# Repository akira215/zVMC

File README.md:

# zVMC
Driving ALDES controlled mechanical ventilation using Modbus, embedded sofware on dedicated PCB using ESP32C6 µC

# Description

This repository contain all the development for an electronic device that will monitor ALDES VMC Inspirair using zigbee to transmit data to a coordinator. It contains: 
 * A PCB design [PCB design](PCB/README.md)
 * An enclosure design to be printed in 3D [Enclosure design](3Dprint/README.md)
 * Source code of the embedded software on the board (in an ESP32C6 µC)
 * An External converter for Zigbee2MQTT service [external converter](external_converters)

# Principle

The board will collect data from various sensors surch as:
 * Upstream static pressure (pump side)
 * Downstream static pressure (home side) - difference between upstream and downstream static pressure is used to estimate filters clogging
 * Water level sensor, to estimate the available water volume in the tank
 * water pulse meter to count the consumption in the home
 * Additionally on board temperature sensor could be monitor

 The 3 first sensors shall be 4-20mA sensor directly connected to the board. The water counter shall be a dry contact meter, connected to the board

 All these sensors have a calibration factor that can be updated directly form Zigbee2MQTT GUI. To avoid losing calibration, the device itself will keep updated theses factor in its Non Volatile Storage.

A 4-20mA input is available for any other futher sensor requirement. Adding a sensor will require to :
 * Update the embedded software
 * Update the external converter on Zigbee2MQTT side

## Usage

  * Short press button to join the zigbee network (coordinator shall grant pairing) -> LED shall flash, until network is joined, it then shutoff
  * Long press button to leave network. When the LED is fixed on, the device is not connected to the network neither is trying to join

## Sensor selection

### Upstream and downstream static pressure

  Regular pressure transmitter are not so expensive and efficient for that purpose. These 2 sensors shall have a measured range according to installation pressure. In regular network, pressure is limited to 3 bars, so selecting a sensor 0-5 bars seems a good choice. If the upper value is higher, the resolution of the measurement will be less as the ADC converter resolution is fixed.

  The shunt to convert current to tension for the ADC converter is 133R, and Imax for the sensor @max range will be 20mA so Umax for ADS1115 will be 2.66V (U=R*I). 5 bars = 500 kPa, so the calibration factor shall be 500 kPa / 2.66V = 187.97 kPa/V. Of course this factor shall be adjusted by measuring at the same location of one sensor the pressure, and correcting the reading of the sensor, but this short computation can help to start setting up calibration factor

### Water level

  Whatever technology of sensor could be used as soon as its output is 4-20mA current. Tests have been done using submerged differential pressure sensor, with the balance pipe to get the atmospheric pressure that run with the electrical cable, they worked properly. The range of this sensor shall be in accordance with the depth of the tank. The output value of Zigbee2MQTT will be a % of depth (meaning 100% when tank is full). Depending on the shape and cross section of the tank, this could be converted to a volume directly in the Z2M external converter, or outside Z2M in another software.

  The shunt to convert current to tension for the ADC converter is 133R, and Imax for the sensor @max range will be 20mA so Umax for ADS1115 will be 2.66V (U=R*I). fFr 100% the calibration factor shall be 100% / 2.66V = 37.594 %/V. Of course this factor shall be adjusted when tank is full to read 100% in the Zigbee2MQTT output.

### Water pulse counter

  The water meter shall send a pulse each XX L, whatever XX is. It is expected to have a dry contact that switch on and off each pulse. Hardware debouncer has been implemented for a particular counter, measuring bouncing using an oscilloscope. Computation of this RC filter has been provided here:
  [Spreadsheet](<PCB/2024-06-29 Comput.ods>)
    
  The kFactor to be set up in Zigbee2MQTT is only the L per pulse of the counter.

## Zigbee2MQTT integration

### External converter

External converter shall be loaded according to Zigbee2MQTT instructions:

[Zigbee2MQTT external converters](https://www.zigbee2mqtt.io/advanced/more/external_converters.html)

Restart Zigbee2MQTT `Webpage > Settings > Tools > Restart Zigbee2MQTT`

### Pairing zTank device

If the LED is fixed on, short press one time on the button, this will put the device in pairing mode.
Device is in Pairing Mode when the LED flahes quickly. 

Put Coordinator (or other device) in pairing mode using Zigbee2MQTT GUI (antenna symbol on the upper right of the screen with mention `All`)

After a short time, LED shall stop flashing. When LED is off, device is paired. You can check on Zigbee2MQTT device list

### Device icon

To add an icon in Zigbee2MQTT GUI, create a folder named `device_icon` in the root of Zigbee2MQTT docker installation (folder containing `configuration.yml`). In that foler, put the `zTank_icon.png` file contained in the `img` directory of this repository.

On Zigbee2MQTT GUI, go to `Devices` list and click on the device. Go to `Settings` tab and scroll down to the `icon` box.
Put `device_icons/zTank_icon.png` in that box. Icon shall be visible on Zigbee2MQTT GUI.

### Reporting

To develop*******************************************************************

## Build Instructions

The embedded software required `esp-ash-components`:

```
git submodule add https://github.com/akira215/esp-ash-components.git components
```

Create a partition.csv for zigbee and configure menuconfig with custom partition table (shall be done by default)

## Remote USB over IP to debug

### Server side using raspberry Pi

Install package:

```
sudo apt install usbip
```

Install drivers and let them run at start:

```
sudo -i
modprobe usbip_host
echo 'usbip_host' >> /etc/modules
```

List usb devices:

```
usbip list -l
```

Create start and stop scripts:

```
nano /usr/sbin/usbip_start.sh
```

```
#! /bin/bash

usb1='303a:1001'
# usb2='xxx'

/usr/sbin/usbip bind --$(/usr/sbin/usbip list -p -l | grep '#usbid='$usb1'#' | cut '-d#' -f1)
#/usr/sbin/usbip bind --$(/usr/sbin/usbip list -p -l | grep '#usbid='$usb2'#' | cut '-d#' -f1)

```

```
nano /usr/sbin/usbip_stop.sh
```

```
#! /bin/bash

usb1='303a:1001'
# usb2='xxx'

/usr/sbin/usbip unbind --$(/usr/sbin/usbip list -p -l | grep '#usbid='$usb1'#' | cut '-d#' -f1)
#/usr/sbin/usbip unbind --$(/usr/sbin/usbip list -p -l | grep '#usbid='$usb2'#' | cut '-d#' -f1)
killall usbipd
```

Turn them executables:

```
chmod +x /usr/sbin/usbip_start.sh
chmod +x /usr/sbin/usbip_stop.sh
```

Test the scripts:

```
. /usr/sbin/usbip_start.sh
. /usr/sbin/usbip_stop.sh
```

Create a service:

```
nano /lib/systemd/system/usbipd.service
```

```
[Unit]
Description=usbip host daemon
After=network.target

[Service]
Type=forking
ExecStart=/usr/sbin/usbipd -D
ExecStartPost=/bin/sh -c '/usr/sbin/usbip_start.sh'
ExecStop=/bin/sh -c '/usr/sbin/usbip_stop.sh'

[Install]
WantedBy=multi-user.target
```

Start the service at boot:
let system know about that service

```
systemctl --system daemon-reload
```

to start service at boot

```
systemctl enable usbipd.service
```

and start service, check status:

```
systemctl start usbipd.service
systemctl status usbipd.service
```

### Client side Windows 11

Create a restore point on the system

Install OSSign release of https://github.com/vadimgrn/usbip-win2 :

https://github.com/OSSign/vadimgrn--usbip-win2/releases

run the GUI to find the device !

## Configuration

Configuration is available in `menuconfig` in the `Project setting` section:

### Pin Layout

  This section refer to hardware connection of LED button and volume meter. <span style="color:red">**These settings shall not be changed unless new hardware is developped.**</span>

### Zigbee endpoints

  This section refer to the endpoint for each sensor of the device. Any change in this number require to update the external converter accordingly

  And in Zigbee2MQTT external converter:

### Zigbee device

  Zigbee stack has been sized doing extensive tests. <span style="color:red">**This setting shall not be changed.**</span>

### ADS Pin Layout

  This section refer to hardware connection of ADS1115 converter to µC pin. <span style="color:red">**These settings shall not be changed unless new hardware is developped.**</span>

### ADS Converter config

  The first 3 inputs refer to the channel in which each sensor is connected. Take care that channel are not implemented on the connector in a logical order, so please refer to pictures that describe which pins of the connector is connected to which ADC channel (and polarity for sensors)

  The delay between 2 queries of ADS is the update rate of the measurement. Between 2 measurement, ADS is put in sleep to optimize consumption. Take care that driver will trigger one conversion for each channel, so there is a minimal time between 2 queries, depending on the resolution set for the ADS.

  The delay between 2 queries of temperature is the update rate of the measurement of the internal µC temperature sensor.

## Current Status

Still work in progress, but is completely running. All bugs 
could be reported to try to improve it.

## PCB design

[PCB design](PCB/README.md)

## Enclosure design design

[Enclosure design](3Dprint/README.md)

## Caveats

### To be developped

OTA update

## Usage and Examples

## Changes

### New in version 0.0.0

## Credits

 * [Zigbee2MQTT](https://github.com/Koenkk/zigbee2mqtt)

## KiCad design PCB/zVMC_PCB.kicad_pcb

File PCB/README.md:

# zTank PCB
A dedicated PCB using ESP32C6 µC as been designed to optimize reliability and costs.

## Tools

 The design of the PCB has been done with KiCad 9.0. Particular footprint and 3D STEP file are included in the `/footprints` folder for sake of maintenance

## Design

 The design is based on ESP32C6 WROOM with the following peripherials:
 * USB for power, flash device and output serial debug / info.
 * Powering circuit is done using MCP1826S 
 * A 4-20mA loop is built based on a LM2735X (1.6MHz) to raise voltage to about 20V
 * 4 channels 4-20mA sensors is provided and converted using ADS1115IDGS. It communicate with µC with i2c port
 * a debounced contact is provided for pulse counter
 * A push button is also provided for very simple HMI
 * PCB is also equipped by a LED for simpl HMI
 * Finally PCB is equipped with header that can be used for a touchscreen device in case of future needs (software lib already written and tested)

 Component size has been selected to 0805, except ESD protective diodes that are smaller.

### USB

  USB socket is grounded to the main ground planes (2 sides).
  USB Lines `USB-` and `USB+` are directly connected to ESP32C6 to flash and monitor µC.
  `VBUS` is used to provide `+5V` (which is in fact lower than +5V) via a protective diode `D3`.

  All this 3 lines are protected by ESD protective diode.

### Voltage regulator

  All the board is powered using `+3.3V`. This voltage is provided by a fixed low-voltage regulator MCP1826S-3302E that can provide up to 1000mA.
  Fixed voltage regulator requires only few external component, in this case only capacitors are installed as per datasheet.

### 4-20mA Voltage circuit

  To avoid noise on lines and due to voltage drop at each stage, 4-20mA loop voltage shall be at around 20V. Care shall be taken when changing this voltage as it may require adjustment (in the shunt values for instance) to avoid damaging other components.

  This voltage is produced from `+5V` using a boost type regulator LM2735X (@1.6MHz). Computation of the external components are provided in the LibreOffice Spreadsheet [PCB comput spreadsheet](<2024-06-29 Comput.ods>). A 33µH inductance has been selected to get a clean output voltage to avoid noise on sensors line.

### 4-20mA conversion

  4 channels are available via Phoenix contact 8 poles connector. Each channel input current is injected in a 133R shunt (low tolerance resistor) to output a voltage below 3.3V. A 100nF capacitor is provided to reduce noise.

  Each channel voltage is then converted in a digital signal using an ADS1115IDGS, that communicate with µC using i2c protocol. A ready pin is used to trigger an interrupt to the µC when data are available.
  External components are:
   * 10k resistor connected to the ground for the address of the device (only one on board so gnd is the common one)
   * 10k pull-up resistor on each signal (`SCL`, `SDA`, `RDY`) connected to µC
   * Decoupling capacitor for power lines and rearmable fuse to protect circuit

### Debounced contact

An harware RC filter has been set up on this input to avoid false triggering. The computation of this filter is detailed in the spreadsheet file [PCB comput spreadsheet](<2024-06-29 Comput.ods>), bouncing duration has been measured using an oscilloscope in a unique water meter equiped with dry contact pulse output. It may be required to adjust this filter if the water meter seems to input false pulse to the µC. 

The only other component is a pull-up resistor to not let a float input.

### µC ESP32C6 WROOM

ESP32C6 power up is done using decoupling capacitor (10µF // 100nF).

The `EN` pin is driven to the `+3.3V` to enable the µC. 

`GPIO9` shall be pulled up to `+3.3V` to set the µC in normal execution mode (instead of ROM serial bootloader when `GPIO9` is pulled to the ground). Despite the doc says that it has an internal pull-up, µC will not boot normally after reporg if not driven to `+3.3V`.

`GPIO8` shall be driven to `+3.3V` as doc says, in order to enter the serial bootloader reliably.

### Push Button

Push button has been connected to `GPIO9`, so it can be used to boot/flash device by driving the pin low. Indeed, no operation is required on this button to flash µC using USB directly, and push button is used by software for HMI purpose.

### Led

A led is connected to `GPIO23` for HMI purpose as well. Resistor has been calculated according to LED spec to grant the required current.

### Header

A header is available to drive a touchscreen if required. It has not been integrated in the enclosure of this repo. It was planned and tested using a ILI9341 TFT touchscreen.

## PCB fabrication

Gerber files are included for fabrication. A batch of PCB has been produced by JLCPCB with the following configuration:

|Base Material        |	FR-4	                             | Layers                     |	2                 |
|---------------------|------------------------------------|----------------------------|-------------------|
|Dimension            |	49 mm* 91 mm                       | PCB Qty                    |	20                |
|Product Type         |	Industrial/Consumer electronics    | Different Design           |	1                 |
|Delivery Format      |	Single PCB	                       | PCB Thickness              |	1.6mm             |
|Specify Stackup      |	no	                               | Layer Sequence             |                   |	
|PCB Color            |	Purple	                           | Silkscreen                 |	White             |
|Material Type        |	TG135	                             | Via Covering               |	Tented            |
|Surface Finish       |	ENIG Gold Thickness: 1U"	         | Deburring/Edge rounding    |	No                |
|Outer Copper Weight  |	1 oz	                             | Gold Fingers               |	No                |
|Electrical Test      |	Flying Probe Fully Test	           | Castellated Holes          |	no                |
|Edge Plating         |	No	                               | Mark on PCB	              | Order Number      |
|Blind Slot           |	No	                               | Min via hole size/diameter |	0.3mm/(0.4/0.45mm)|
|4-Wire Kelvin Test   |	No	                               | Paper between PCBs         |	No                |
|Appearance Quality   |	IPC Class 2 Standard	             | Confirm Production file    |	No                |
|Silkscreen Technology|	Ink-jet/Screen Printing Silkscreen | Package Box                |	With JLCPCB logo  |
|Inspection Report    |	No	                               | Board Outline Tolerance    |	±0.2mm(Regular)   |
|UL Marking           |	No	                               | Countersink Hole           |	No                |

## Assembly

A stencil as been produced by JLCPCB, so the assembly has been done using solder paste, manually placing components, and reflow is done using an hot plate.

The components that generate issues during that process are:
 * USB connector `J5` : often some bridges are created due to the high density of pin. It has to be manually fixed
 * ESD protection diodes `D4`, `D5` & `D6`: are they are really small and light, they moved during the reflow process. It has to be manually fixed with a soldering iron, as hot air gun make them move anyway whaterver the airflow is
 * Care should be taken on the pin of ADS converter `U1`(bridges) and µC `U4` (alke of solder)
 * Obviously connector `J1`, `J2` and `J3` have to be solded manually

## Usage

For routing simplicity, 4-20mA channels are not reparted logically on the board, please consider the scheme here below.

Debounced pulse contact don't have polarity.

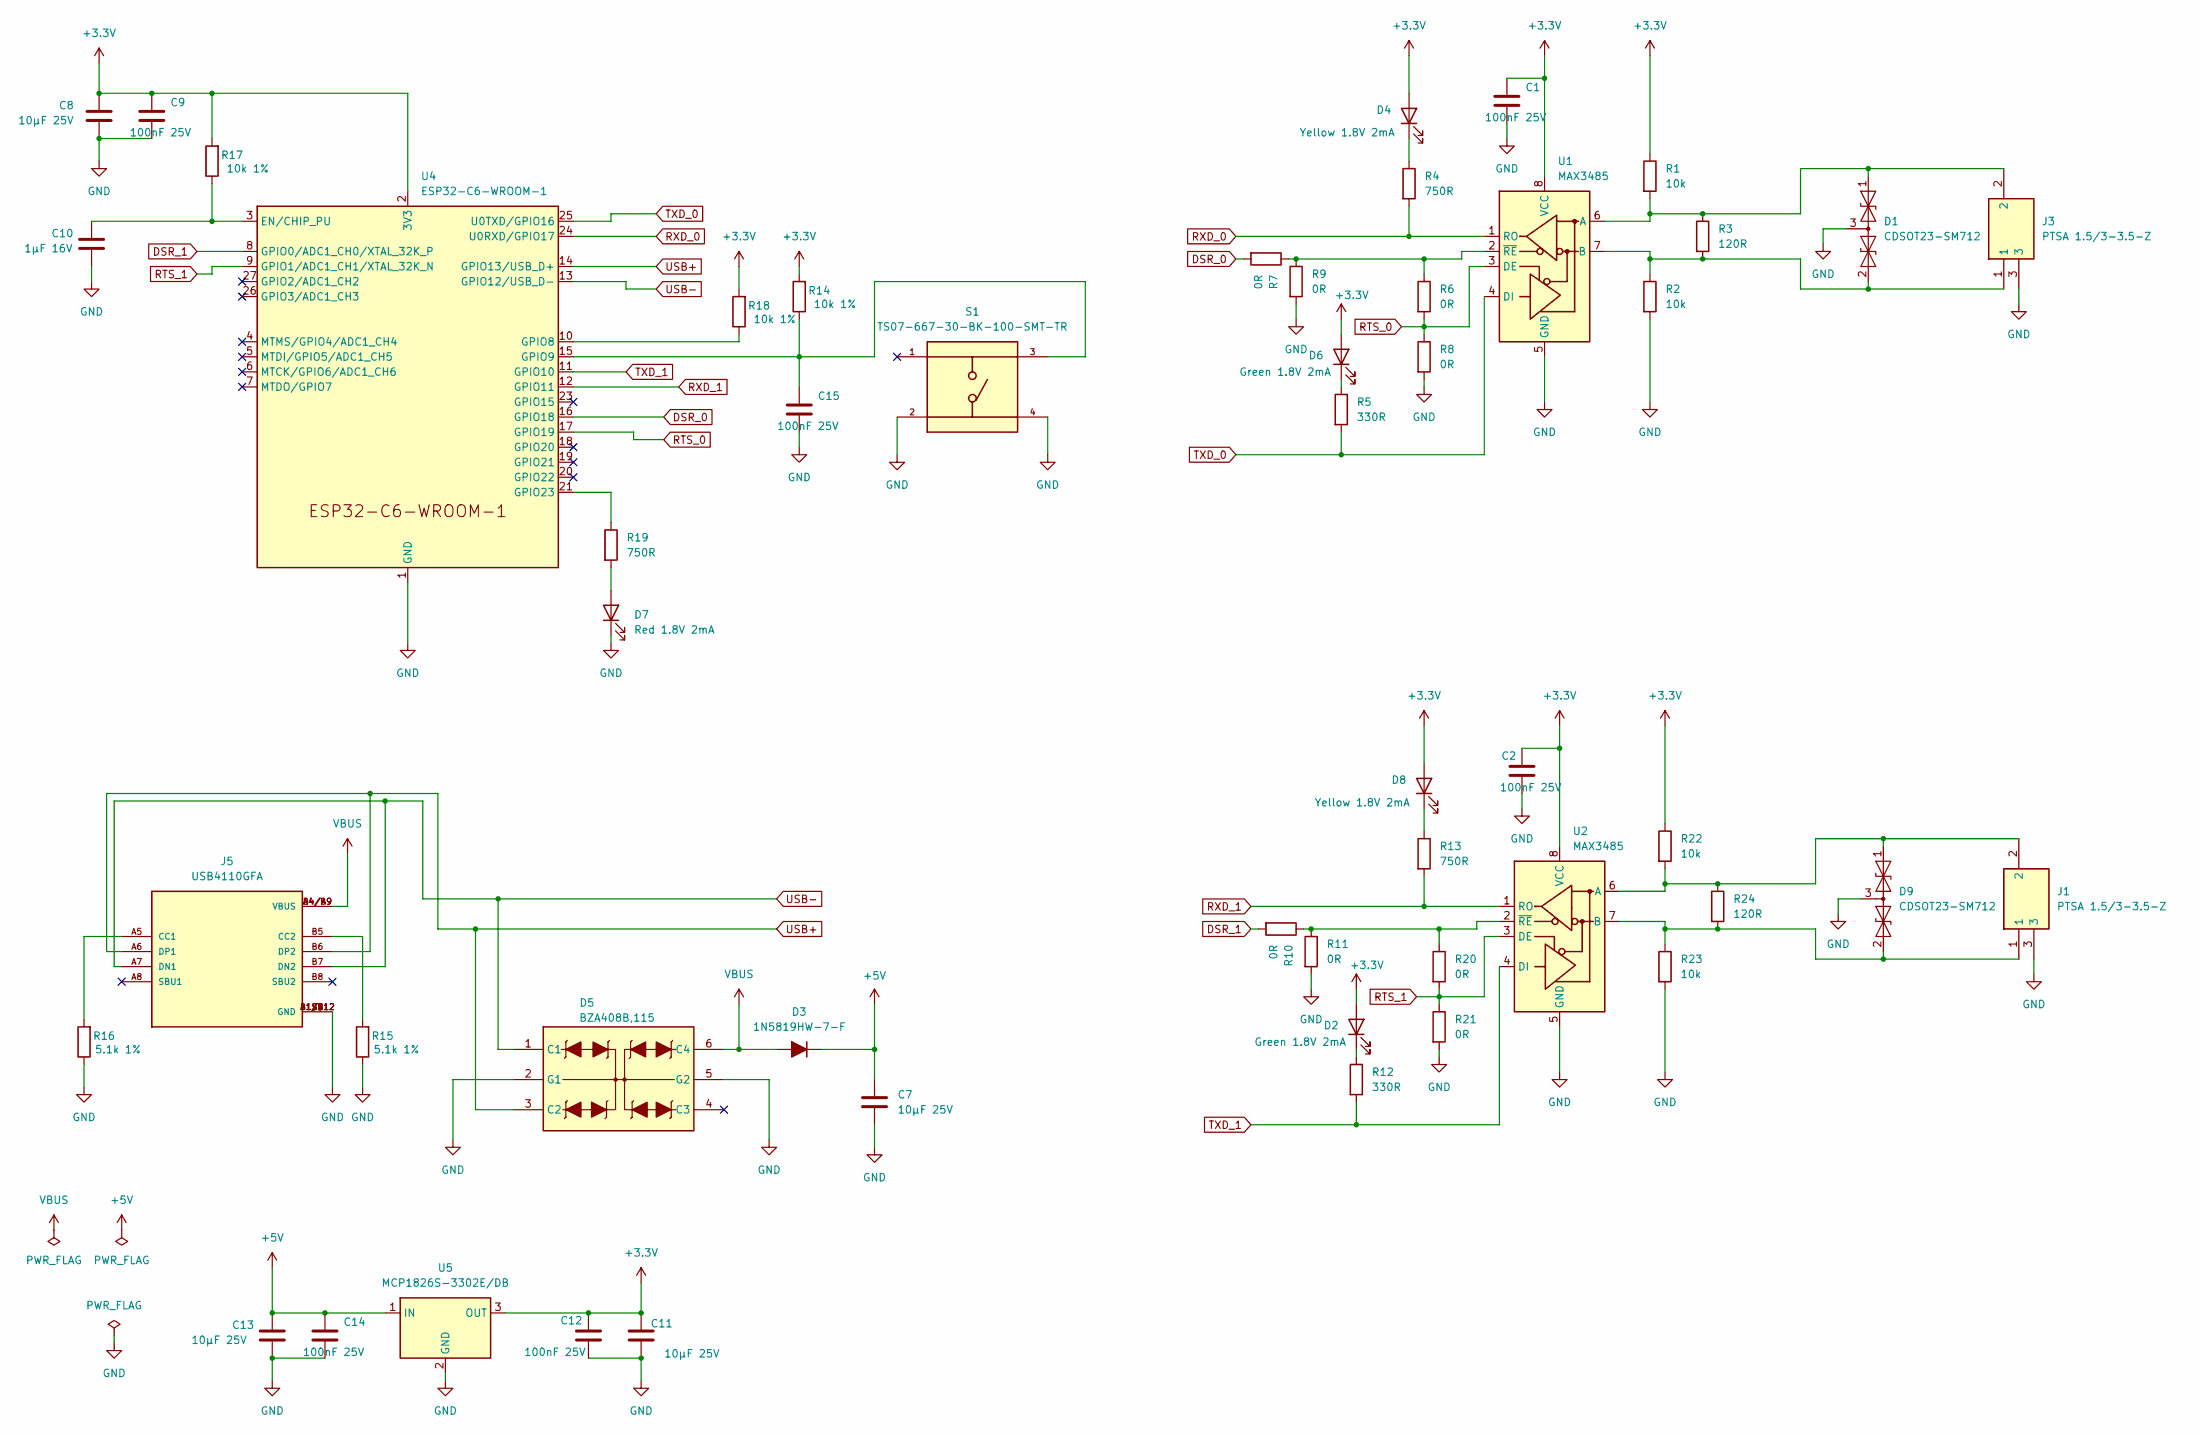
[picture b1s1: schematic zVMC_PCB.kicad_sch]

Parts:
C1, C2, C9, C12, C14, C15: 100nF 25V; C_0805_2012Metric
C7, C8, C11, C13: 10µF 25V; C_0805_2012Metric
C10: 1µF 16V; C_0805_2012Metric
D1, D9: CDSOT23-SM712; SOT-23
D2, D6: Green 1.8V 2mA; D_0805_2012Metric
D3: 1N5819HW-7-F; D_SOD-123
D4, D8: Yellow 1.8V 2mA; D_0805_2012Metric_Pad1.15x1.40mm_HandSolder
D5: BZA408B,115; SOT95P275X110-6N; Mouser Part Number 771-BZA408B,125
D7: Red 1.8V 2mA; D_0805_2012Metric
J1, J3: PTSA 1.5/3-3.5-Z; Phoenix Contact PTSA 3; Mouser Part Number 651-1985205
J5: USB4110GFA; GCT_USB4110GFA
R1, R2, R22, R23: 10k; R_0805_2012Metric
R3, R24: 120R; R_0805_2012Metric
R4, R13, R19: 750R; R_0805_2012Metric
R5, R12: 330R; R_0805_2012Metric
R6, R7, R8, R9, R10, R11, R20, R21: 0R; R_0805_2012Metric
R14, R17, R18: 10k 1%; R_0805_2012Metric
R15, R16: 5.1k 1%; R_0805_2012Metric
S1: TS07-667-30-BK-100-SMT-TR; CUI switch SW_TS07-667-30-BK-100-SMT-TR; PARTREV 1.0
U1, U2: MAX3485; SOIC-8_3.9x4.9mm_P1.27mm
U4: ESP32-C6-WROOM-1
U5: MCP1826S-3302E/DB; SOT-223-3_TabPin2

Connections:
+3.3V: C1.1, C2.1, C8.1, C9.1, C11.1, C12.1, D2.2 (A), D4.2 (A), D6.2 (A), D8.2 (A), R1.1, R14.2, R17.2, R18.2, R22.1, U1.8 (VCC), U2.8 (VCC), U4.2 (3V3), U5.3 (OUT)
+5V: C7.1, C13.1, C14.1, D3.1 (K), U5.1 (IN)
DSR_0: R7.2, U4.16 (GPIO18)
DSR_1: R10.2, U4.8 (GPIO0/ADC1_CH0/XTAL_32K_P)
GND: C1.2, C2.2, C7.2, C8.2, C9.2, C10.2, C11.2, C12.2, C13.2, C14.2, C15.2, D1.3 (common), D5.2 (G1), D5.5 (G2), D7.1 (K), D9.3 (common), J1.3, J3.3, J5.A1/B12 (GND), J5.B1/A12 (GND), J5.S1 (GND), J5.S2 (GND), J5.S3 (GND), J5.S4 (GND), R2.2, R8.2, R9.2, R11.2, R15.1, R16.1, R21.2, R23.2, S1.2, S1.4, U1.5 (GND), U2.5 (GND), U4.1 (GND), U4.28 (GND), U4.29 (GND), U5.2 (GND)
unnamed: D1.1 (A1), J3.2, R1.2, R3.1, U1.6 (A)
unnamed: D1.2 (A2), J3.1, R2.1, R3.2, U1.7 (B)
unnamed: D2.1 (K), R12.1
unnamed: D4.1 (K), R4.1
unnamed: D6.1 (K), R5.1
unnamed: D7.2 (A), R19.2
unnamed: D8.1 (K), R13.1
unnamed: D9.1 (A1), J1.2, R22.2, R24.1, U2.6 (A)
unnamed: D9.2 (A2), J1.1, R23.1, R24.2, U2.7 (B)
unnamed: J5.A5 (CC1), R16.2
unnamed: J5.B5 (CC2), R15.2
unnamed: R6.1, R7.1, R9.1, U1.2 (~RE)
unnamed: R10.1, R11.1, R20.1, U2.2 (~RE)
unnamed: C10.1, R17.1, U4.3 (EN/CHIP_PU)
unnamed: R18.1, U4.10 (GPIO8)
unnamed: C15.1, R14.1, S1.3, U4.15 (GPIO9)
unnamed: R19.1, U4.21 (GPIO23)
RTS_0: R6.2, R8.1, U1.3 (DE), U4.17 (GPIO19)
RTS_1: R20.2, R21.1, U2.3 (DE), U4.9 (GPIO1/ADC1_CH1/XTAL_32K_N)
RXD_0: R4.2, U1.1 (RO), U4.24 (U0RXD/GPIO17)
RXD_1: R13.2, U2.1 (RO), U4.12 (GPIO11)
TXD_0: R5.2, U1.4 (DI), U4.25 (U0TXD/GPIO16)
TXD_1: R12.2, U2.4 (DI), U4.11 (GPIO10)
USB+: D5.3 (C2), J5.A6 (DP1), J5.B6 (DP2), U4.14 (GPIO13/USB_D+)
USB-: D5.1 (C1), J5.A7 (DN1), J5.B7 (DN2), U4.13 (GPIO12/USB_D-)
VBUS: D3.2 (A), D5.6 (C4), J5.A4/B9 (VBUS), J5.B4/A9 (VBUS)

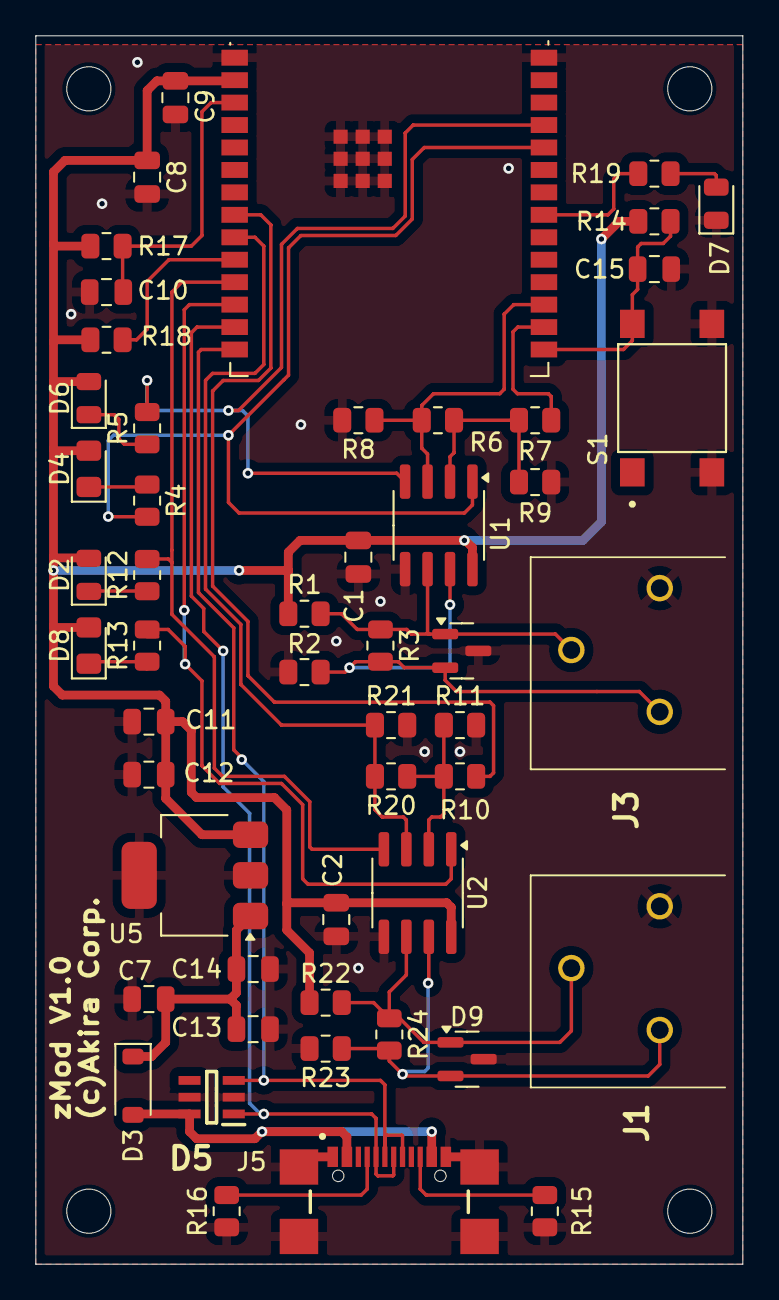
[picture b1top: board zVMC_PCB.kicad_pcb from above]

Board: 2 copper layers, 40.0 x 69.5 mm, 52 parts (0 on the bottom side), 31 nets.

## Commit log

2025-10-04 First Commit PCB
2025-10-07 Updating Mouser BOM adue to Maxim supply restrictions
2025-10-07 USB over IP using RPi server and Win client
2025-10-08 Creating templates
2025-10-08 updating components
2025-10-14 adding 3D printing enclosure
2025-10-15 WIP on MOdbus
2025-10-17 WIP Modbus. Communication working
2025-10-18 Implementing aldes driver
2025-10-19 starting algo aldes driver
2025-10-20 working on aldes driver
2025-10-21 All registers implemented
2025-10-21 reverse engineering date time 32 bit format
2025-10-24 writing tests
2025-10-25 Temperatures clusters ok
2025-10-26 working on tempo filter
2025-11-13 add custom filter attr
2025-11-15 custom attr for filters
2025-11-15 Filter tempo working full
2025-11-15 Filter cluster full ok
2025-11-15 Speed settings WIP
2025-11-15 Speed setting ok missing VMC modbus update
2025-11-20 airflow ok, bypass position and season to be reported
2025-11-21 first release
2025-11-21 Sharing docs
2025-11-21 Adjustement on external converter
2026-01-02 Revise README to clarify project scope
    Updated project description to reflect focus on ALDES VMC Inspirair.
2026-05-28 Add min and max values for Filter_Elapsed_Days
